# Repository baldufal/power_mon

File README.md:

# PowerMon
A **9-channel power monitoring and control board** based on the [INA3221](https://www.ti.com/product/INA3221) current sensor and an [ESP32-C3 super mini](https://www.espboards.dev/esp32/esp32-c3-super-mini/) running (a custom compiled version of) [Tasmota](https://tasmota.github.io/).

## Features
- 9 individually controllable output channels
- Each channel can be permanently enabled/disabled using jumpers
- LEDs indicating the output state of each channel
- Power sensing for each individual channel
- -5 ~ 28V output voltage (shared between all outputs)
- 3 integrated fuse holders (5x20mm)

## Board
The board was designed using KiCad 9.
It uses custom symbols and footprints which can be found in the [footprints](footprints) directory.

Care should be taken that the right versions of the ESP32-C3 Super Mini and the INA3221 are selected (see below).
The voltage is regulated using a compact 5V volatage regulator module.

[Schematics](images/schematics_overview.png)
[Schematics for outputs](images/schematics_outputs.png)
[PCB](images/pcb.png)

The board was fabricated by [JLCPCB](https://jlcpcb.com/) and soldered by hand.

### BOM
| Qty | Part |
| --- | --- |
| 1 | **ESP32-C3 Super Mini** (there are [two versions](https://roryhay.es/blog/esp32-c3-super-mini-flaw)) |
| 3 | **INA3221 module** (the [_old version_](https://youtu.be/tCXCQwTQt9Q?si=c6mN08hn90Hn1HyM) with shared GND) |
| 1 | 5V voltage regulator [module](https://de.aliexpress.com/item/1005008257960729.html?spm=a2g0o.order_list.order_list_main.133.3af95c5fQgkEpP&gatewayAdapt=glo2deu) |
| 3 | 5x20mm fuse holder |
| 9 | SOT23 n-Channel FET like [SI2302](https://www.vishay.com/docs/68645/si2302cds.pdf) / A2SHB |
| 9 | 3mm LED with resistors |
| 9 | pin header with 3 poles + jumpers |
| 2 | pin header with 8 poles |
| 13 | 5.08mm terminal blocks with 2 poles |

## Tasmota compilation
As INA3221 support is not enabled in any of the precompiled Tasmota versions, a [custom compiled](https://github.com/tasmota/docs/blob/master/docs/Compile-your-build.md) Tasmota is used.

1. Download the latest version of [Tasmota](https://github.com/arendst/Tasmota) and open it in [PlatformIO](https://platformio.org/).
2. Enable I2C and INA3221 drivers in **tasmota/user_config_override.h** by inserting
```
#ifndef USE_I2C
#define USE_I2C
#endif

#ifndef USE_INA3221
#define USE_INA3221
#endif
```
3. In **platformio_override.ini** change _default_envs_ to `tasmota32c3` and _board_ to `esp32c3`.
4. Compile and upload.

## Tasmota configuration
To configure the freshly flashed Tasmota:

First, [connect it to your wifi](https://tasmota.github.io/docs/Getting-Started/#__tabbed_2_2).

Then, set a **static IP** using the console for a more stable connection ([see the docs](https://tasmota.github.io/docs/Commands/#wi-fi)):
```
ipaddress1 <host IP address>
ipaddress2 <gateway IP address>
ipaddress3 <subnet mask>
ipaddress4 <DNS 1 IP>
ipaddress5 1.1.1.1
```

Then **disable the feature that resets everything** if a `Button` is pressed for 5 seconds:
```
SetOption1 1
```

Then set the **pin configuration**:

Then create a [rule](https://tasmota.github.io/docs/Rules/) that [**configures the INA3221 sensors**](https://staars.github.io/docs/Commands/#sensors) after startup:
```
Rule1 ON System#Boot DO Sensor100 1, 0.1, 0.1, 0.1 ENDON ON System#Boot DO Sensor100 2, 0.1, 0.1, 0.1 ENDON ON System#Boot DO Sensor100 3, 0.1, 0.1, 0.1 ENDON
```
and enable it:
```
Rule1 1
```

Optionally, configure the number of decimals using
```
VoltRes 2
AmpRes 3
WattRes 2
```

## See also
[Here](https://github.com/arendst/Tasmota/discussions/16660) is a discussion of INA3221 configuration in Tasmota.

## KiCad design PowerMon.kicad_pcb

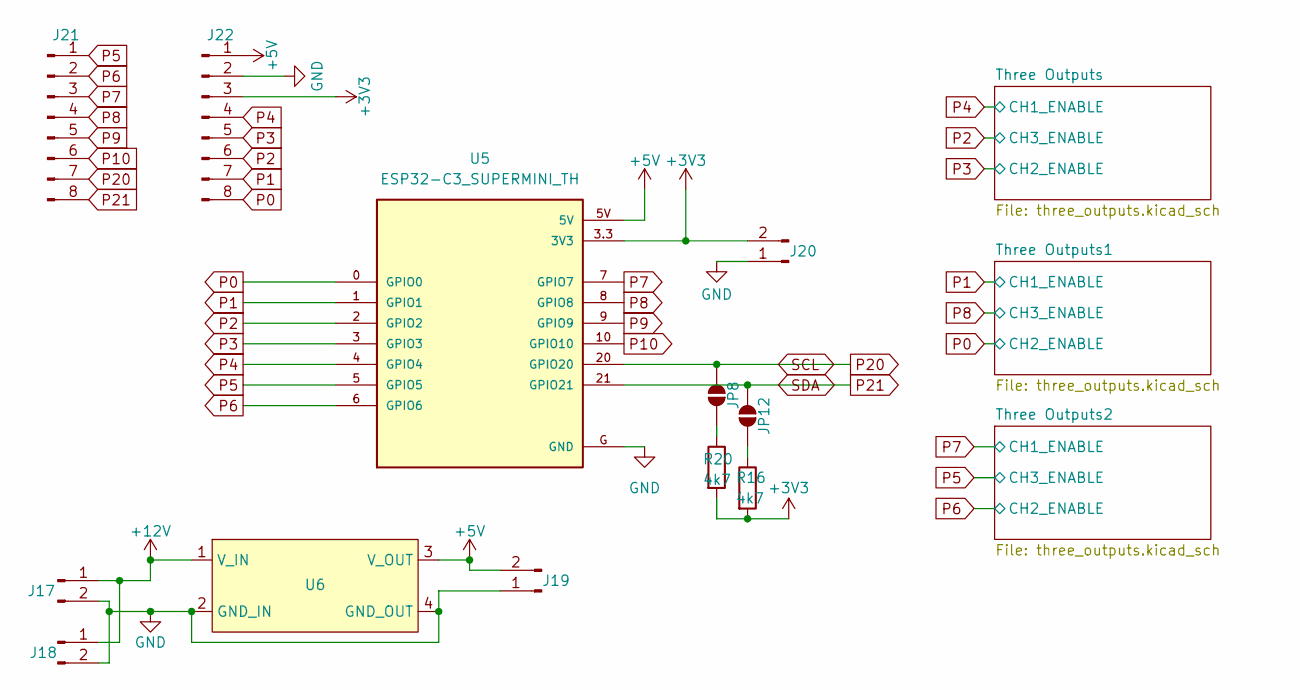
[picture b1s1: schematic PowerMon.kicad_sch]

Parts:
J17, J18, J19, J20: Conn_01x02_Pin; TerminalBlock_Phoenix_MKDS-3-2-5.08_1x02_P5.08mm_Horizontal
J21, J22: Conn_01x08_Pin; PinHeader_1x08_P2.54mm_Vertical
JP8, JP12: SolderJumper_2_Open; SolderJumper-2_P1.3mm_Open_RoundedPad1.0x1.5mm
R16, R20: 4k7; R_0805_2012Metric_Pad1.20x1.40mm_HandSolder
U5: ESP32-C3_SUPERMINI_TH; MODULE_ESP32-C3_SUPERMINI_TH
U6: DC_DC_3A_Mini_Aliexpress

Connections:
+3V3: J20.2, J22.3, R16.2, R20.2, U5.3.3 (3V3); also elsewhere on the board
+5V: J19.2, J22.1, U5.5V, U6.3 (V_OUT)
+12V: J17.1, J18.1, U6.1 (V_IN); also elsewhere on the board
GND: J17.2, J18.2, J19.1, J20.1, J22.2, U5.G (GND), U6.2 (GND_IN), U6.4 (GND_OUT); also elsewhere on the board
unnamed: JP8.1 (A), R20.1
unnamed: JP12.1 (A), R16.1
P0: J22.8, U5.0 (GPIO0); also elsewhere on the board
P1: J22.7, U5.1 (GPIO1); also elsewhere on the board
P2: J22.6, U5.2 (GPIO2); also elsewhere on the board
P3: J22.5, U5.3 (GPIO3); also elsewhere on the board
P4: J22.4, U5.4 (GPIO4); also elsewhere on the board
P5: J21.1, U5.5 (GPIO5); also elsewhere on the board
P6: J21.2, U5.6 (GPIO6); also elsewhere on the board
P7: J21.3, U5.7 (GPIO7); also elsewhere on the board
P8: J21.4, U5.8 (GPIO8); also elsewhere on the board
P9: J21.5, U5.9 (GPIO9)
P10: J21.6, U5.10 (GPIO10)
P20: J21.7, JP8.2 (B), U5.20 (GPIO20); also elsewhere on the board
P21: J21.8, JP12.2 (B), U5.21 (GPIO21); also elsewhere on the board

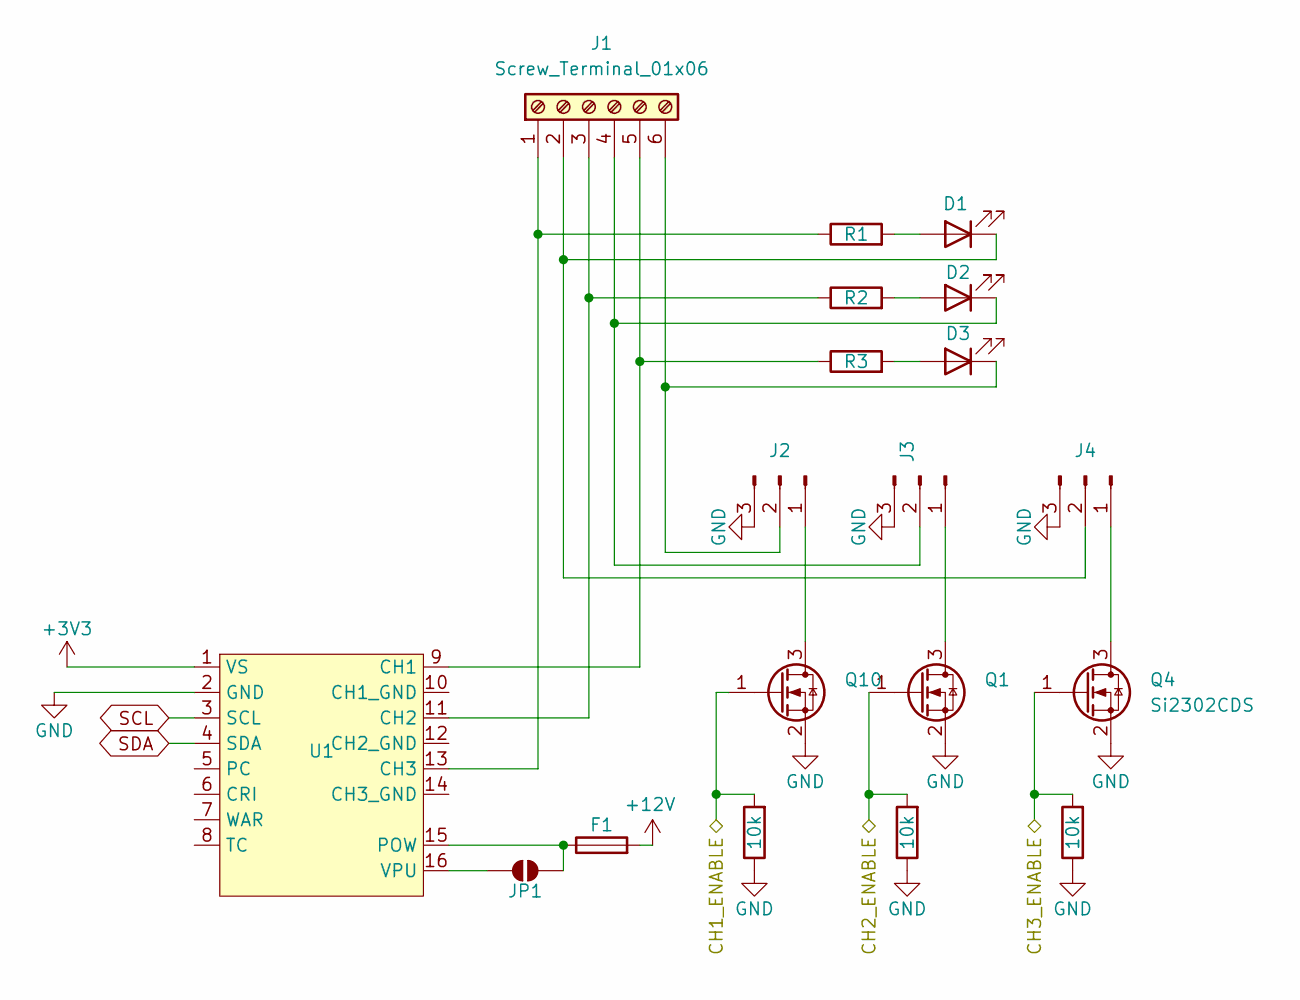
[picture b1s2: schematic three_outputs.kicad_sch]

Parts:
D1, D2, D3: LED; LED_D3.0mm
F1: Fuse; Fuse Holder 15mm pin distance 5x20
J1: Screw_Terminal_01x06; TerminalBlock_Phoenix_MKDS-3-6-5.08_1x06_P5.08mm_Horizontal
J2, J3, J4: Conn_01x03_Pin; PinHeader_1x03_P2.54mm_Vertical
JP1: SolderJumper_2_Open; SolderJumper-2_P1.3mm_Open_RoundedPad1.0x1.5mm
Q1, Q4, Q10: Si2302CDS; SOT-23
R1, R2, R3: R; R_0805_2012Metric_Pad1.20x1.40mm_HandSolder
R13, R18, R23: 10k; R_0805_2012Metric_Pad1.20x1.40mm_HandSolder
U1: INA3221_Module

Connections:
+3V3: U1.1 (VS); also elsewhere on the board
+12V: F1.2; also elsewhere on the board
GND: J2.3, J3.3, J4.3, Q1.2 (S), Q4.2 (S), Q10.2 (S), R13.1, R18.1, R23.1, U1.2 (GND); also elsewhere on the board
unnamed: D1.2 (A), R1.2
unnamed: D1.1 (K), J1.2, J4.2
unnamed: D2.2 (A), R2.2
unnamed: D2.1 (K), J1.4, J3.2
unnamed: D3.2 (A), R3.2
unnamed: D3.1 (K), J1.6, J2.2
unnamed: J1.1, R1.1, U1.13 (CH3)
unnamed: J1.3, R2.1, U1.11 (CH2)
unnamed: J1.5, R3.1, U1.9 (CH1)
unnamed: J2.1, Q10.3 (D)
unnamed: J3.1, Q1.3 (D)
unnamed: J4.1, Q4.3 (D)
unnamed: JP1.1 (A), U1.16 (VPU)
unnamed: F1.1, JP1.2 (B), U1.15 (POW)
P2: Q4.1 (G), R23.2; also elsewhere on the board
P3: Q1.1 (G), R18.2; also elsewhere on the board
P4: Q10.1 (G), R13.2; also elsewhere on the board
P20: U1.3 (SCL); also elsewhere on the board
P21: U1.4 (SDA); also elsewhere on the board

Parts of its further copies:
D4, D5, D6, D7, D8, D9: LED; LED_D3.0mm
F2, F3: Fuse; Fuse Holder 15mm pin distance 5x20
J5, J9: Screw_Terminal_01x06; TerminalBlock_Phoenix_MKDS-3-6-5.08_1x06_P5.08mm_Horizontal
J6, J7, J8, J10, J11, J12: Conn_01x03_Pin; PinHeader_1x03_P2.54mm_Vertical
JP2, JP3: SolderJumper_2_Open; SolderJumper-2_P1.3mm_Open_RoundedPad1.0x1.5mm
Q2, Q3, Q5, Q6, Q11, Q12: Si2302CDS; SOT-23
R4, R5, R6, R7, R8, R9: R; R_0805_2012Metric_Pad1.20x1.40mm_HandSolder
R14, R15, R19, R21, R24, R25: 10k; R_0805_2012Metric_Pad1.20x1.40mm_HandSolder
U2, U3: INA3221_Module

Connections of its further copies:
+3V3: U2.1 (VS), U3.1 (VS); also elsewhere on the board
+12V: F2.2, F3.2; also elsewhere on the board
GND: J6.3, J7.3, J8.3, J10.3, J11.3, J12.3, Q2.2 (S), Q3.2 (S), Q5.2 (S), Q6.2 (S), Q11.2 (S), Q12.2 (S), R14.1, R15.1, R19.1, R21.1, R24.1, R25.1, U2.2 (GND), U3.2 (GND); also elsewhere on the board
unnamed: D4.2 (A), R4.2
unnamed: D4.1 (K), J5.2, J8.2
unnamed: D5.2 (A), R5.2
unnamed: D5.1 (K), J5.4, J7.2
unnamed: D6.2 (A), R6.2
unnamed: D6.1 (K), J5.6, J6.2
unnamed: D7.2 (A), R7.2
unnamed: D7.1 (K), J9.2, J12.2
unnamed: D8.2 (A), R8.2
unnamed: D8.1 (K), J9.4, J11.2
unnamed: D9.2 (A), R9.2
unnamed: D9.1 (K), J9.6, J10.2
unnamed: J5.1, R4.1, U2.13 (CH3)
unnamed: J5.3, R5.1, U2.11 (CH2)
unnamed: J5.5, R6.1, U2.9 (CH1)
unnamed: J6.1, Q11.3 (D)
unnamed: J7.1, Q2.3 (D)
unnamed: J8.1, Q5.3 (D)
unnamed: J9.1, R7.1, U3.13 (CH3)
unnamed: J9.3, R8.1, U3.11 (CH2)
unnamed: J9.5, R9.1, U3.9 (CH1)
unnamed: J10.1, Q12.3 (D)
unnamed: J11.1, Q3.3 (D)
unnamed: J12.1, Q6.3 (D)
unnamed: JP2.1 (A), U2.16 (VPU)
unnamed: F2.1, JP2.2 (B), U2.15 (POW)
unnamed: JP3.1 (A), U3.16 (VPU)
unnamed: F3.1, JP3.2 (B), U3.15 (POW)
P0: Q2.1 (G), R19.2; also elsewhere on the board
P1: Q11.1 (G), R14.2; also elsewhere on the board
P5: Q6.1 (G), R25.2; also elsewhere on the board
P6: Q3.1 (G), R21.2; also elsewhere on the board
P7: Q12.1 (G), R15.2; also elsewhere on the board
P8: Q5.1 (G), R24.2; also elsewhere on the board
P20: U2.3 (SCL), U3.3 (SCL); also elsewhere on the board
P21: U2.4 (SDA), U3.4 (SDA); also elsewhere on the board

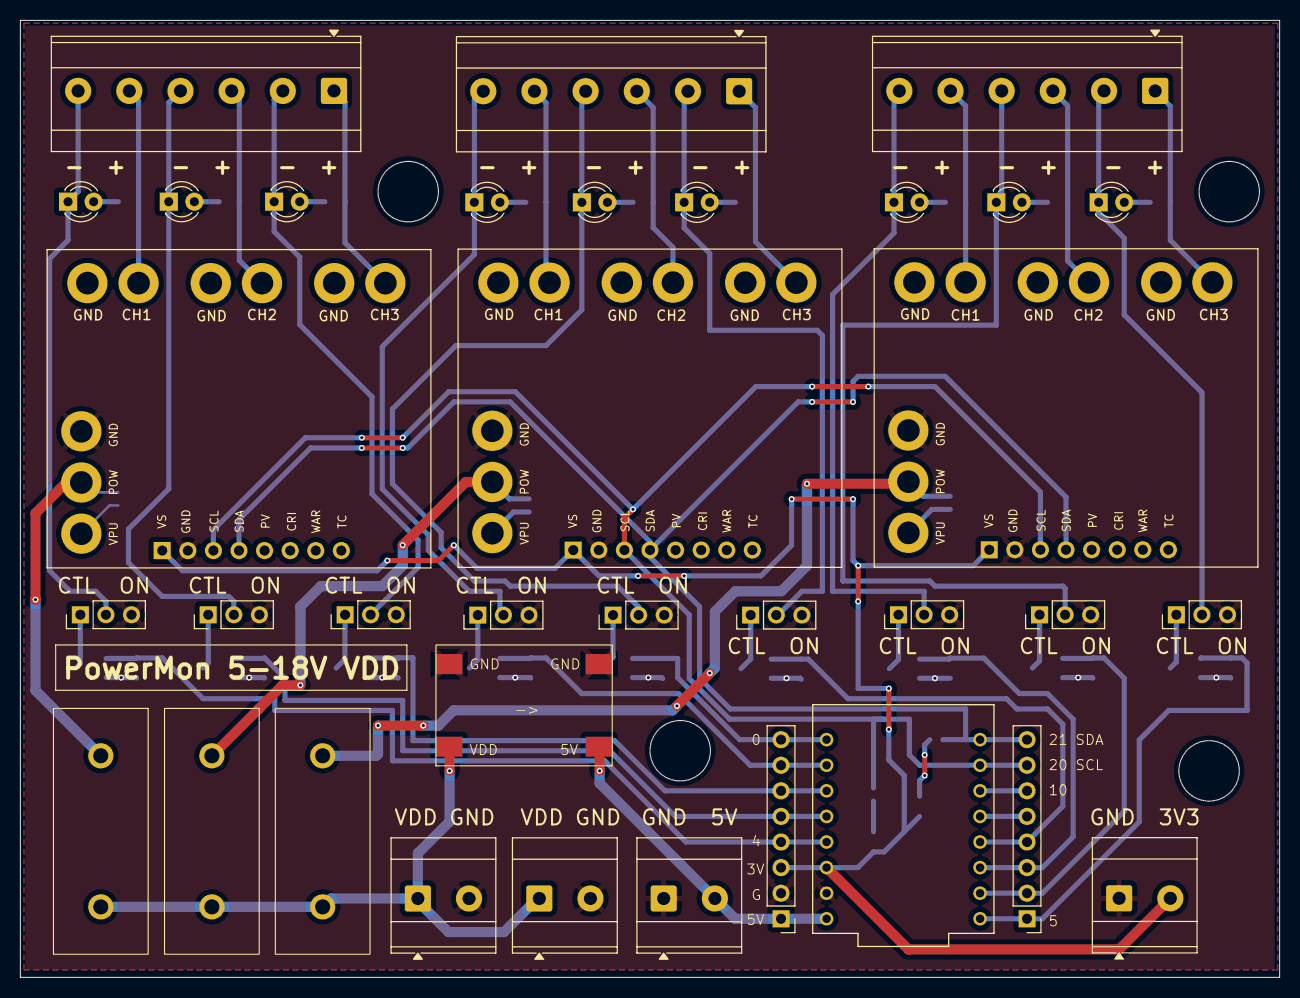
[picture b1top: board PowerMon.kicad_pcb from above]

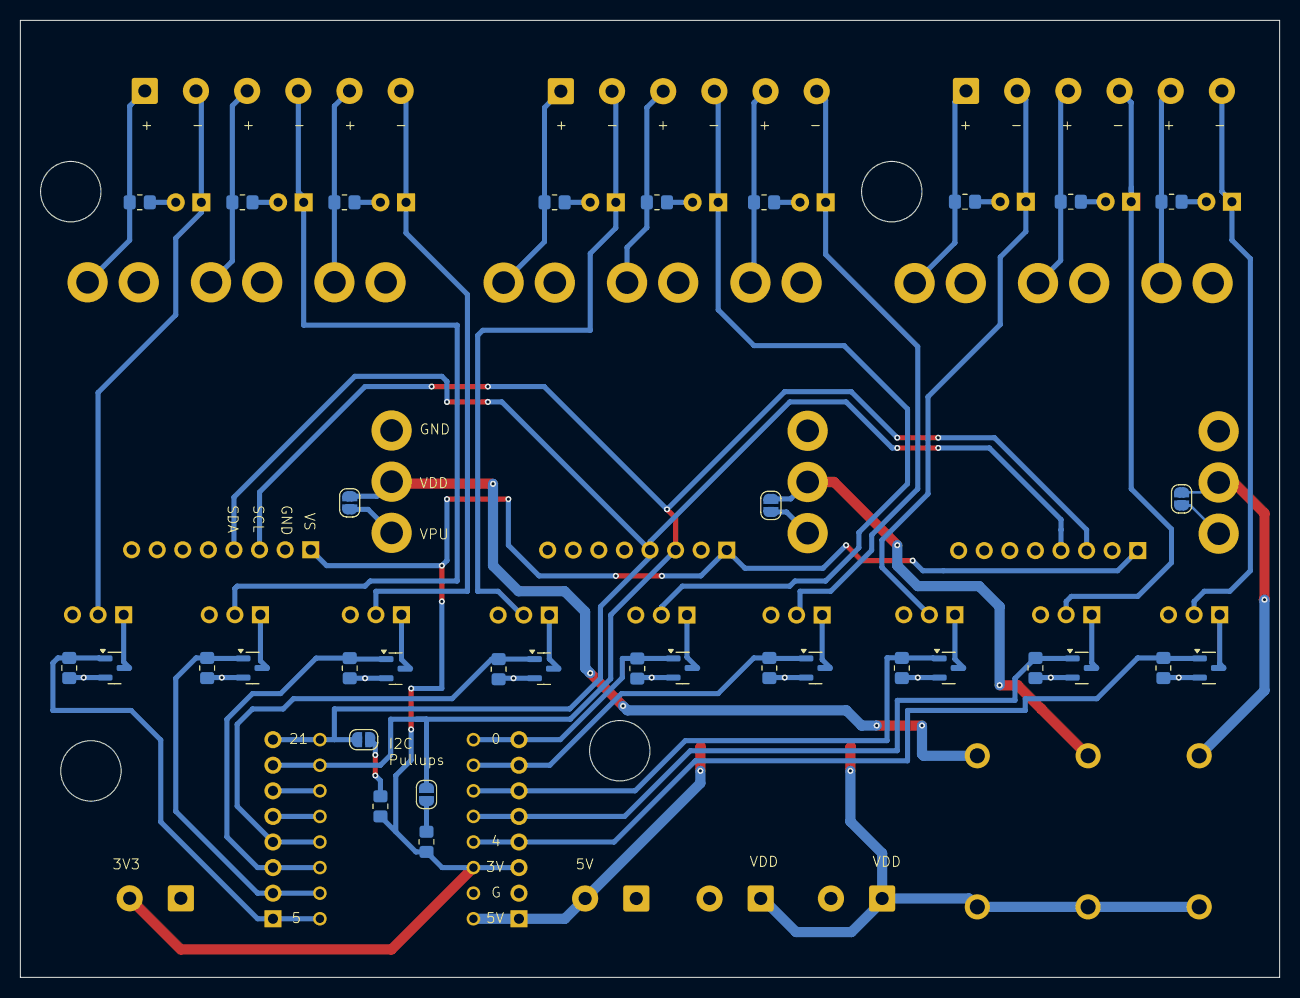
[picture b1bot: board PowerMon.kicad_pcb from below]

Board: 2 copper layers, 125.0 x 95.0 mm, 69 parts (34 on the bottom side), 61 nets.

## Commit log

2025-10-15 Add readme
2025-10-16 Update README with PowerMon details and instructions
    Added detailed information about the PowerMon board, including features, board design, BOM, and Tasmota compilation instructions.
2025-10-16 Add pin config
2025-10-16 Revise README for improved structure and details
    Updated README to enhance clarity and formatting.
2025-10-16 Revise README for clarity and formatting
